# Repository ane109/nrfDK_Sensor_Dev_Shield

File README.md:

# nrfDK_Sensor_Dev_Shield
Sensor shield compatible with nRFDK and Arduino development boards

## Details
- Test platform for sensors intended for use on an IoT wearable
- Interfaces directly with an nRF9160DK development board over I2C
- Contains a heart rate monitor, 9-DOF IMU, and coulomb counter with reversible current
- Test points for all signals and voltages

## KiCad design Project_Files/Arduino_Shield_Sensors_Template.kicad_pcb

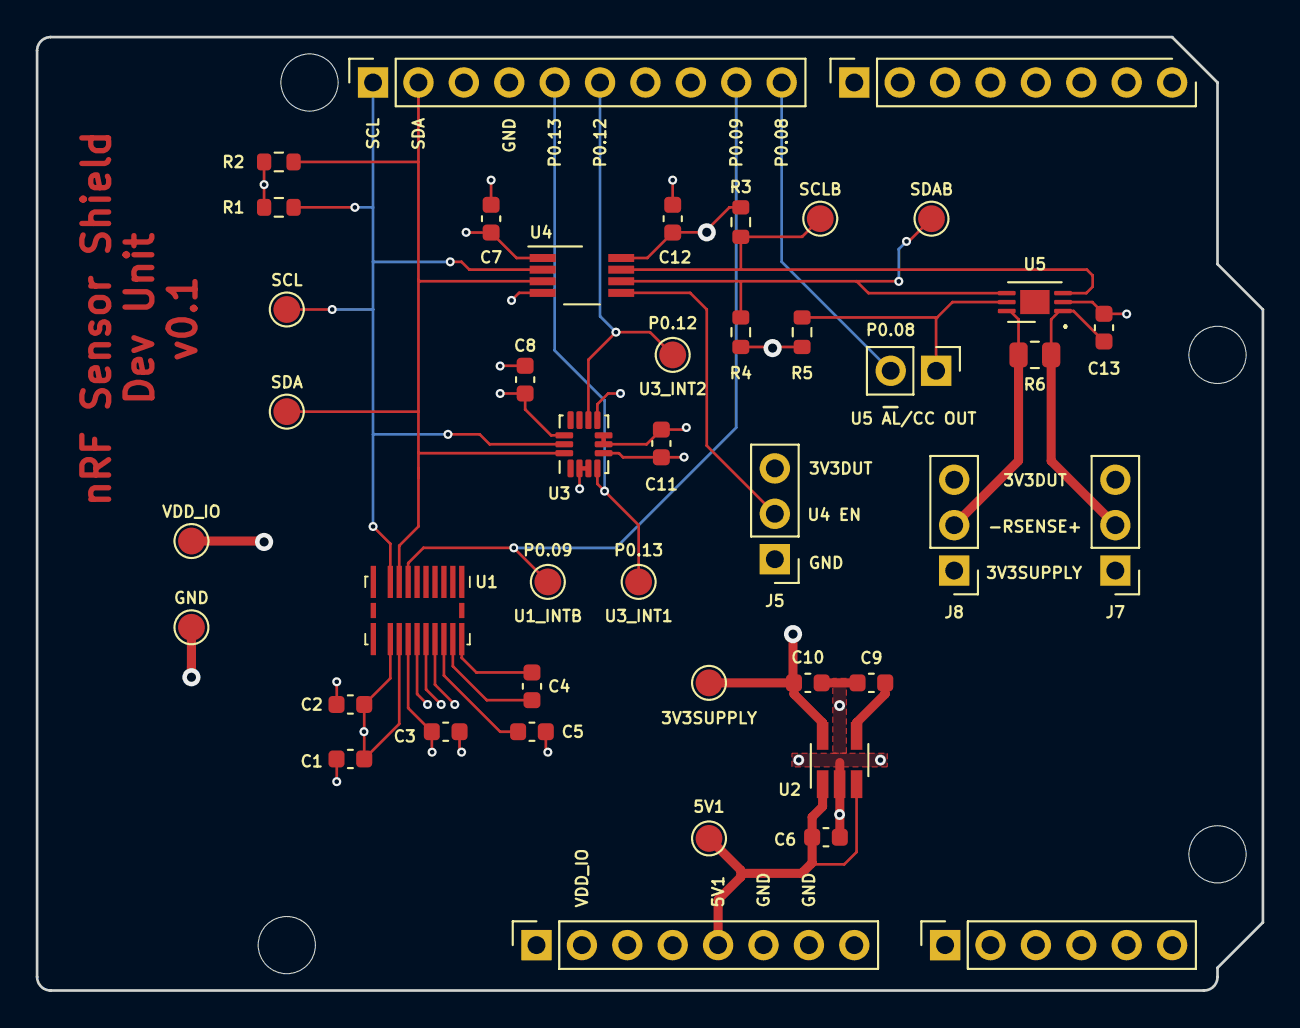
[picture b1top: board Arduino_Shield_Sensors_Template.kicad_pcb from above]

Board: 4 copper layers, 68.6 x 53.3 mm, 47 parts (0 on the bottom side), 21 nets.

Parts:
3V3SUPPLY, 5V1: TestPoint; TestPoint_Pad_D1.5mm
C1, C2, C3, C4, C5, C6, C7, C10, C12: 1uF; C_0603_1608Metric
C8, C11, C13: 0.1uF; C_0603_1608Metric
C9: 0.01uF; C_0603_1608Metric
GND: TestPoint; TestPoint_Pad_D1.5mm
J1: Power; PinSocket_1x08_P2.54mm_Vertical
J2: Digital/PWM; PinSocket_1x10_P2.54mm_Vertical
J3: Analog; PinSocket_1x06_P2.54mm_Vertical
J4: Digital/PWM; PinSocket_1x08_P2.54mm_Vertical
J5, J7, J8: Conn_01x03_Pin; PinHeader_1x03_P2.54mm_Vertical
MH1, MH2, MH3, MH4: MountingHole_3.2mm
R1, R2, R3, R4, R5: 4.7k; R_0603_1608Metric
R6: 0.075; R_0805_2012Metric
SCL: TestPoint; TestPoint_Pad_D1.5mm
SCLB: TestPoint; TestPoint_Pad_D1.5mm
SDA: TestPoint; TestPoint_Pad_D1.5mm
SDAB: TestPoint; TestPoint_Pad_D1.5mm
U1: MAX86150EFF; MAX86150_extended
U1_INTB, U3_INT1, U3_INT2: TestPoint; TestPoint_Pad_D1.5mm
U2: LP3985; SOT-23-5_HandSoldering
U3: LSM6DSL; LSM6DSL_extended
U4: TCA9617A; VSSOP-8_3.0x3.0mm_P0.65mm
U5: LTC2942; LTC2942_Extended
U5 AL/CC OUT: Conn_01x02_Pin; PinHeader_1x02_P2.54mm_Vertical
VDD_IO: TestPoint; TestPoint_Pad_D1.5mm

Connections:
3V3dut: C3.2, C12.1, J5.3, J7.3, J8.3, R3.1, R4.1, R5.1, U1.15 (VLED), U4.8 (VCCB)
3V3supply: 3V3SUPPLY.1, C10.1, J7.1, J8.1, U2.5 (OUT)
5V1: 5V1.1, C6.1, J1.5, U2.1 (IN), U2.3 (EN)
GND: C1.1, C2.1, C3.1, C5.1, C6.2, C7.2, C8.1, C9.2, C10.2, C11.2, C12.2, C13.1, GND.1, J1.6, J1.7, J2.4, J5.1, U1.16 (PGND), U1.17 (GND_DIG), U1.18 (GND_ANA), U2.2 (GND), U3.2 (SDX), U3.3 (SCX), U3.6 (GND), U3.7 (GND), U4.4 (GND), U5.2 (GND)
unnamed: J5.2, U4.5 (EN)
unnamed: R5.2, U5.5 (~AL/CC), U5 AL/CC OUT.1
unnamed: C13.2, J7.2, R6.1, U5.1 (SENSE+)
unnamed: J8.2, R6.2, U5.6 (SENSE-)
unnamed: C4.1, U1.20 (C1_N)
unnamed: C4.2, U1.21 (C1_P)
unnamed: C5.2, U1.19 (VREF)
unnamed: C9.1, U2.4 (BYPASS)
unnamed: R3.2, SCLB.1, U4.7 (SCLB), U5.3 (SCL)
unnamed: R4.2, SDAB.1, U4.6 (SDAB), U5.4 (SDA)
P0.08: J2.10, U5 AL/CC OUT.2
P0.09: J2.9, U1.7 (INTB), U1_INTB.1
P0.12: J2.6, U3.9 (INT2), U3_INT2.1
P0.13: J2.5, U3.4 (INT1), U3_INT1.1
SCL: J2.1, R1.2, SCL.1, U1.9 (SCL), U3.13 (SCL), U4.2 (SCLA)
SDA: J2.2, R2.2, SDA.1, U1.8 (SDA), U3.14 (SDA), U4.3 (SDAA)
Vdd_IO: C1.2, C2.2, C7.1, C8.2, C11.1, J1.2, R1.1, R2.1, U1.13 (VDD_DIG), U1.14 (VDD_ANA), U3.5 (VDDIO), U3.8 (VDD), U3.12 (CS), U4.1 (VCCA), VDD_IO.1

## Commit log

2025-05-28 Added files
    Design notes and images added.
2025-06-23 Organized Files into appropriate folders
2025-06-23 Update README.md
    Added project details, schematic, and photo
